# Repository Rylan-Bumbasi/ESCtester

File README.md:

# ESCtester
PCB design to test motors connected to an ESC using a potentiometer

The objective of this project was to create a convinient way for the SDSU Mechatronics electircal sub-team to efficiently test motors to check if they are working properly.

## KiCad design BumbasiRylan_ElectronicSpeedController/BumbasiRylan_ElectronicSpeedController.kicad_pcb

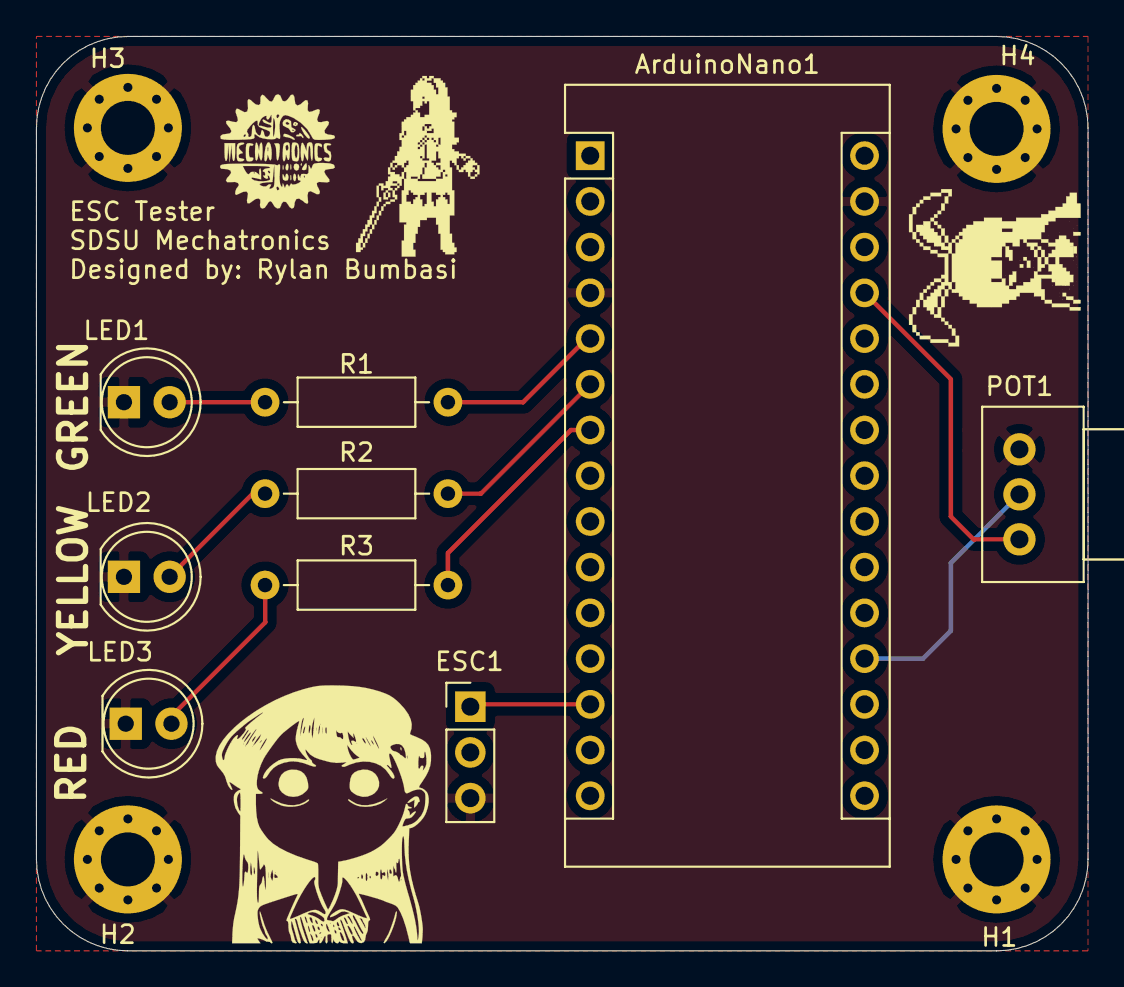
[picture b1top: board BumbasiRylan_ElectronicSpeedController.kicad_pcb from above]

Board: 2 copper layers, 58.4 x 50.8 mm, 13 parts (0 on the bottom side), 10 nets.

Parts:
ArduinoNano1: Arduino_Nano_v3.x; Arduino_Nano
ESC1: Basic ESC; PinHeader_1x03_P2.54mm_Vertical
H1, H2, H3, H4: MountingHole_Pad; MountingHole_3mm_Pad_Via
LED1: GREEN; LED_D5.0mm
LED2: YELLOW; LED_D5.0mm
LED3: RED; LED_D5.0mm
POT1: 100 Ω; Potentiometer_Alps_RK09Y11_Single_Horizontal
R1, R2, R3: 200 Ω; R_Axial_DIN0207_L6.3mm_D2.5mm_P10.16mm_Horizontal

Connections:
/5V: ArduinoNano1.27, POT1.1
/A0: ArduinoNano1.19, POT1.2
/D2: ArduinoNano1.5, R1.1
/D3: ArduinoNano1.6, R2.1
/D4: ArduinoNano1.7, R3.1
/D10(PWM): ArduinoNano1.13, ESC1.1
GND: ArduinoNano1.4, ArduinoNano1.29, ESC1.3, H1.1, H2.1, H3.1, H4.1, LED1.1, LED2.1, LED3.1, POT1.3
unnamed: LED1.2, R1.2
unnamed: LED2.2, R2.2
unnamed: LED3.2, R3.2

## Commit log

2021-09-29 KiCad files for project
    This folder will contain all the KiCad files for this project including the schematic design, PCB footprint and gerber files
2021-09-29 Updated description of project
